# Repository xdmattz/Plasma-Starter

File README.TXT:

Plasma Cutter Pilot Start Circuit

This project is for a circuit that adds a pilot arc function to a cheap chinese plasma cutter. ie. CT520D and others.

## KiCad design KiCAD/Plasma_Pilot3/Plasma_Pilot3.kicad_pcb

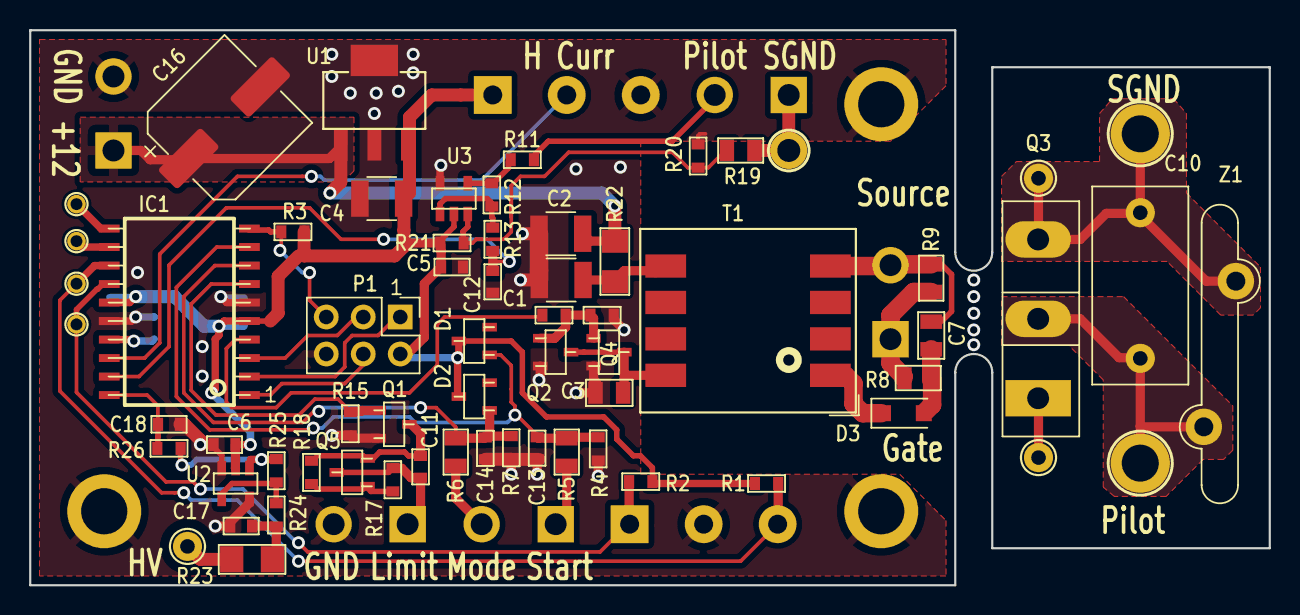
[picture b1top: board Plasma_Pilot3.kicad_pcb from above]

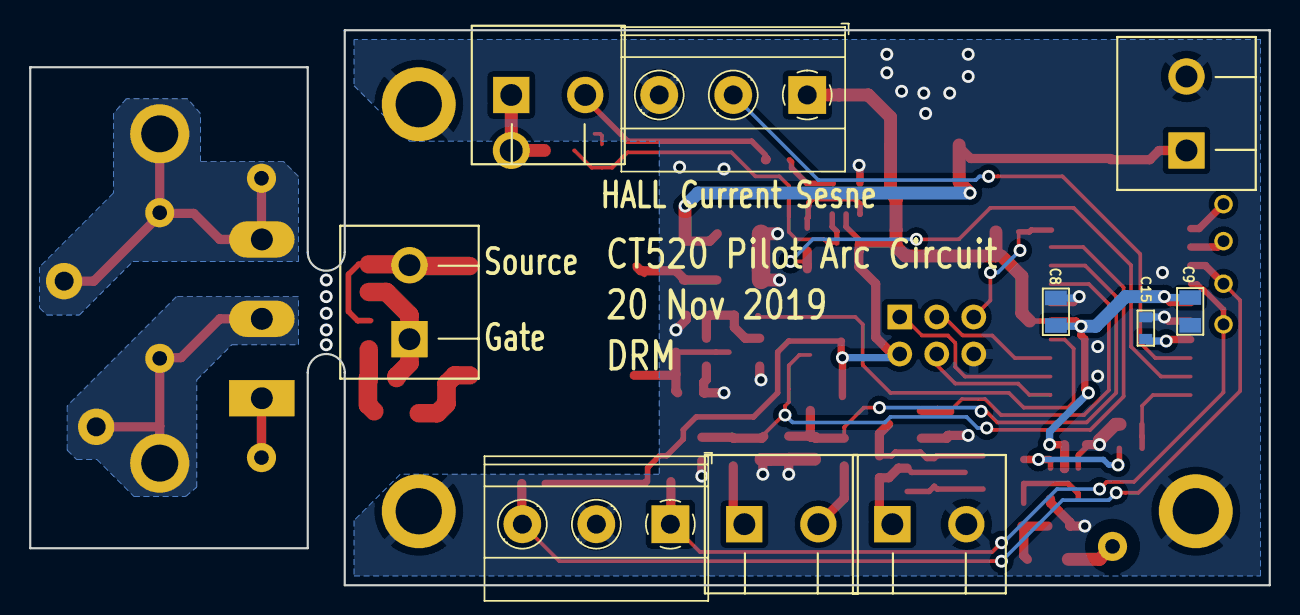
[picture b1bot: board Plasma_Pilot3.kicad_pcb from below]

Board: 2 copper layers, 85.1 x 38.1 mm, 78 parts (10 on the bottom side), 40 nets.

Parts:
C1, C2, C4: 10uF; cap_1210
C3: 1000pF; cap_0805
C5, C6, C11, C13, C14, C15, C17: 0.1uF; cap_0603
C7, C8, C9: 0.1uF; cap_0805
C10: 0.1uF; Cap_Rad_13x6mm
C12, C18: 1000pF; cap_0603
C16: 47uF; CP_Elec_8x6.9
D1, D2: BAV99; sot-23
D3: BAV3004W; D_SOD-123F
IC1: ATTINY861A-S; soic-20
MTG1, MTG2, MTG3: TP; MTG_200_125D
P1: CONN_02X03; PinHeader_2x03_P2.54mm_Vertical
P2, P3, P4, P5, P6: CONN_01X02; TerminalBlock5_08mm_x2
P7, P8: CONN_01X03; TerminalBlock_Phoenix_MKDS-1,5-3-5.08_1x03_P5.08mm_Horizont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
Q1, Q2, Q4: BSS138; sot-23
Q3: Q_NIGBT_GEC; TO-247-3_Vertical
Q5: FMMT3904; SOT-23
R1, R2, R3, R4, R7, R15, R16, R20, R21: 10K; res_0603
R5, R6: 22K; res_0805
R8: 10; res_0805
R9: 4.7K; res_0805
R11, R12, R17, R18, R24, R25, R26: Res6; res_0603
R13: 220; res_0603
R14: 10; res_0603
R19: 1000; res_0805
R22: 10; res_1206
R23: Res6; res_1206
T1: EP10_GDT; EP10_SMT
TP1, TP3, TP4: TP; TP80
TP2, TP10: TP; TP160
TP5: TP; TP100
TP6, TP7, TP8, TP9: TP; TP50
U1: LT1129CST-5; SOT-223
U2, U3: LMC7101; sot-23-5
Z1: MOV; MOV_20mm

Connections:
+12V: C2.1, C16.1, P3.1, R22.2, U1.1
/MISO: IC1.2, P1.1
/MODE: C14.1, D2.1, IC1.8, R6.1, R7.1
/MOSI: IC1.1, P1.4
/SCK: IC1.3, P1.3
/START: C13.1, D1.1, IC1.9, R4.1, R5.1
/~XRESET: IC1.10, P1.5, R3.2
GND: C1.2, C2.2, C3.2, C4.2, C5.2, C6.2, C8.2, C9.2, C12.2, C13.2, C14.2, C15.2, C16.2, C17.1, C18.2, IC1.6, IC1.16, MTG1.1, MTG2.1, MTG3.1, P1.6, P3.2, P4.2, P7.2, P8.3, Q1.2, Q2.2, Q4.2, R4.2, R7.2, R15.2, R16.1, R20.2, U1.2, U1.4, U2.3, U2.5, U3.5
unnamed: C1.1, R22.1, T1.5
unnamed: C3.1, Q2.3, Q4.3, T1.8
unnamed: C7.1, D3.2, R8.1
unnamed: C10.1, P6.2, Q3.2, R11.2, TP10.1, Z1.1
unnamed: C7.2, C10.2, P5.2, Q3.3, R9.2, T1.4, TP2.1, TP3.1, Z1.2
unnamed: C11.1, P4.1, Q5.3, R17.1
unnamed: C11.2, Q1.3, Q5.2, R18.2
unnamed: C12.1, IC1.19, R13.1
unnamed: C15.1, IC1.17
unnamed: C17.2, R23.1, R24.2
unnamed: C18.1, IC1.20, R26.1
unnamed: D3.1, T1.1
unnamed: IC1.4, R14.2
unnamed: IC1.7, Q1.1, R15.1
unnamed: IC1.11, TP9.1
unnamed: IC1.12, TP8.1
unnamed: IC1.13, P7.3, R1.2, TP7.1
unnamed: IC1.14, P7.1, R2.2, TP6.1
unnamed: IC1.18, P8.2
unnamed: P2.1, R5.2
unnamed: P2.2, R6.2
unnamed: P5.1, Q3.1, R8.2, R9.1, TP1.1
unnamed: P6.1, R19.1, TP5.1
unnamed: Q2.1, Q4.1, R14.1, R16.2
unnamed: Q5.1, R17.2, R18.1
unnamed: R11.1, R12.2, U3.4
unnamed: R12.1, R13.2, U3.1
unnamed: R19.2, R20.1, R21.2, U3.3
unnamed: R23.2, TP4.1
unnamed: R24.1, R25.2, U2.4
unnamed: R25.1, R26.2, U2.1
VDD: C4.1, C5.1, C6.1, C8.1, C9.1, D1.3, D2.3, IC1.5, IC1.15, P1.2, P8.1, R1.1, R2.1, R3.1, R21.1, U1.3, U2.2, U3.2

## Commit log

2019-12-04 Added state machine diagram
2019-12-05 Started the next schematic rev Plasma Pilot4
2019-12-05 Added Library Cache
2020-01-18 Added new transformer fixed code to work on CT600 plasma cutter
